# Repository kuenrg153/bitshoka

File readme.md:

```
Open Source is Intrinsic to Bitcoin
```
# The bitshoka V1.0
The Bitshoka V1.0 is based entirely off of the Bitaxe. The only difference are the logos on Schematic and PCB.
Huge shoutout to skot for all the work he did create this project!
The aim Bitshoka V1.0 is to have a Made in Africa Bitcoin miner that works as a platform to get people interested in and familiar with Bitcoin mining.
We hope that this is the first of a number of contributions the Bitshoka team can make to the bitcoin network.

# The bitaxeGamma
bitaxe is a fully open source Bitcoin ASIC miner aimed at decentralizing mining. bitaxeGamma is the 5th major revision of the bitaxe that now includes the BM1370 ASIC from the Antminer S21 Pro

## Goals
- **Easy**: Just plug it in and mine Bitcoin over WiFi. No external computer needed.
- **Practical**: low cost, low noise, low power, low maintenance. You can run this at home.
- **ASIC Power**: High efficiency and hashrate, based on the latest and greatest Application Specific Integrated Circuits.
- **Versatile**: Mine to any StratumV1 pool, Lottery mine, Solo mine, Or hack it to do whatever you want.
- **Bitcoin Ethos**: Fully open source, permissionless and decentralized to support the worldwide freedom money.

## ASIC
At the heart of the bitaxeGamma is a BM1370 Bitcoin mining ASIC from the Antminer S21 Pro from Bitmain. It's not open source.

- Bitmain claims the BM1370 has 15 J/TH efficiency. We can get pretty close to that with the BitaxeGamma
- The Antminer S21 Pro has a nominal hashrate of 234 TH/s. There are 3 hashboards with 65 chips each, for a total of 195 chips. The bitaxeGamma has a single one of these chips. That means _about_ 1.2 TH/s per bitaxeGamma. Initial testing looks good!
- The BM1370 is brand new and isn't available individually yet. The best place to get these chips is right out of a S21 Pro.
- The BM1370 has a different footprint and pinout from the BM1368, BM1366, BM1397 and BM1387 in previous bitaxe.

## Current Status
- BitaxeGamma 600 is working well and has been released!
- In addition to higher hashrate, the Gamma also uses more power. Please pay attemtion to hash frequency and voltage settings as it's much easier to overheat, especially when using the stock heatsink and fan.
- BM1370 firmware support has been added to [esp-miner](https://github.com/skot/esp-miner)
- Be sure to check the [HW issues](https://github.com/skot/bitaxe/issues) for known bugs, reworks and errata.
- This is an _advanced_ build! You can do it, but if you're not looking for a project, it might be best to buy one pre-assembled from one of the [many sellers](https://bitaxe.org/legit.html). Check [Skot's method](assembly.md) of hand assembling PCBs.

## PCB Hardware
This repo contains all of the design files for the PCB. [KiCAD](https://www.kicad.com) software is used. There is a BOM file for all of the components that get soldered to the PCB. 

- Order PCBs from your favorite PCB shop, like [JLCPCB](https://jlcpcb.com), [SeeedStudio](https://www.seeedstudio.com/fusion_pcb.html), or [PCBWay](https://www.pcbway.com)
    - Gerbers are in the `Manufacturing Files` dir. PCBs are 4-layer, 6mil trace/space and 0.3mm hole compatible. 1oz outer / 0.5oz inner layer thickness works well.
    - Make sure to order stencils too. These are the "paste" layers in the gerbers folder. one for top and one for bottom.
- All PCB parts except the ASIC are available from [DigiKey](https://www.digikey.com/en/products) and others. You can find Digikey part numbers on the DK tab of the BOM

## Extra Hardware
There are a few other hardware components that are needed for a complete bitaxe.

- **Heatsink**
	- [40x40mm heatsink and 5V fan](https://www.aliexpress.com/item/2251832861666365.html) from a random AliExpress seller. The fans are crap, but the heatsinks are good.  
- **Fan**
	- You **must** have active cooling on the bitaxe. The heatsink alone is not enough.
	- The Bitaxe has a connector for a 4pin, 5V PWM fan. 40mm square, 20mm thick fans work nicely with the suggested heatsink. Make sure to get a 5V fan! 12V spin, but slowly overheating your Bitaxe..
	- Upgrade your fan with the [Noctua NF-A4x10](https://noctua.at/en/nf-a4x10-5v-pwm) 5V 4-Pin fan for a much more pleasant experience.
- **Thermal compound**
	- Use a good quality thermal compound between the heatsink and ASIC. [Thermal Grizzly Kryonaut](https://www.amazon.com/Thermal-Grizzly-Kryonaut-Grease-Paste/dp/B011F7W3LU) has been known to work well.  
- **Display**
	- Supports 0.91" SSD1306-based I2C OLED Module. [Example Amazon seller](https://www.amazon.com/gp/product/B08ZY4YBHL). Make sure to get the male pins to interface with the Bitaxe PCB. 
- **Power Supply**
	- **5V DC Only!** Anything else will damage the Bitaxe. Be careful and double-check your power supply is 5V. Many other voltage power supplies use the same connector.
	- The power supply needs to supply in excess of 4A (20W) and not drop below 5V. Often times you have to use a power supply rated for 25-30W to get this!
 		- The [Meanwell GST60A05-P1J](https://www.digikey.com/en/products/detail/mean-well-usa-inc/GST60A05-P1J/7703709) at 30 Watts is the cadillac of 5V PSUs and is working well with the Gamma.  
	- The bitaxe uses a 5.5x2.1mm, center-positive barrel jack. 5.5x2.5mm plugs have been known to work.
- **Stand**
	- The PCB has corner mounting holes. You're going to want a stand to mount your Bitaxe. Many excellent 3D printed designs are available.

## Firmware
- The [ESP-Miner](https://github.com/skot/ESP-Miner) has initial support for the BM1370 ASIC. Improvements are ongoing.

### ESP32 Programming Requirements
- As of the bitaxeUltra, all ESP32 programming is done through a USB-C cable and connector on the bitaxe. See [ESP-Miner](https://github.com/skot/ESP-Miner) for more details.

## More Information
- Project page at [bitaxe.org](https://bitaxe.org)
- [Open Source Miners United](discord.gg/osmu) Discord chat
- [building.md](building.md) for PCB ordering tips
- [assembly.md](assembly.md) for assembly tips

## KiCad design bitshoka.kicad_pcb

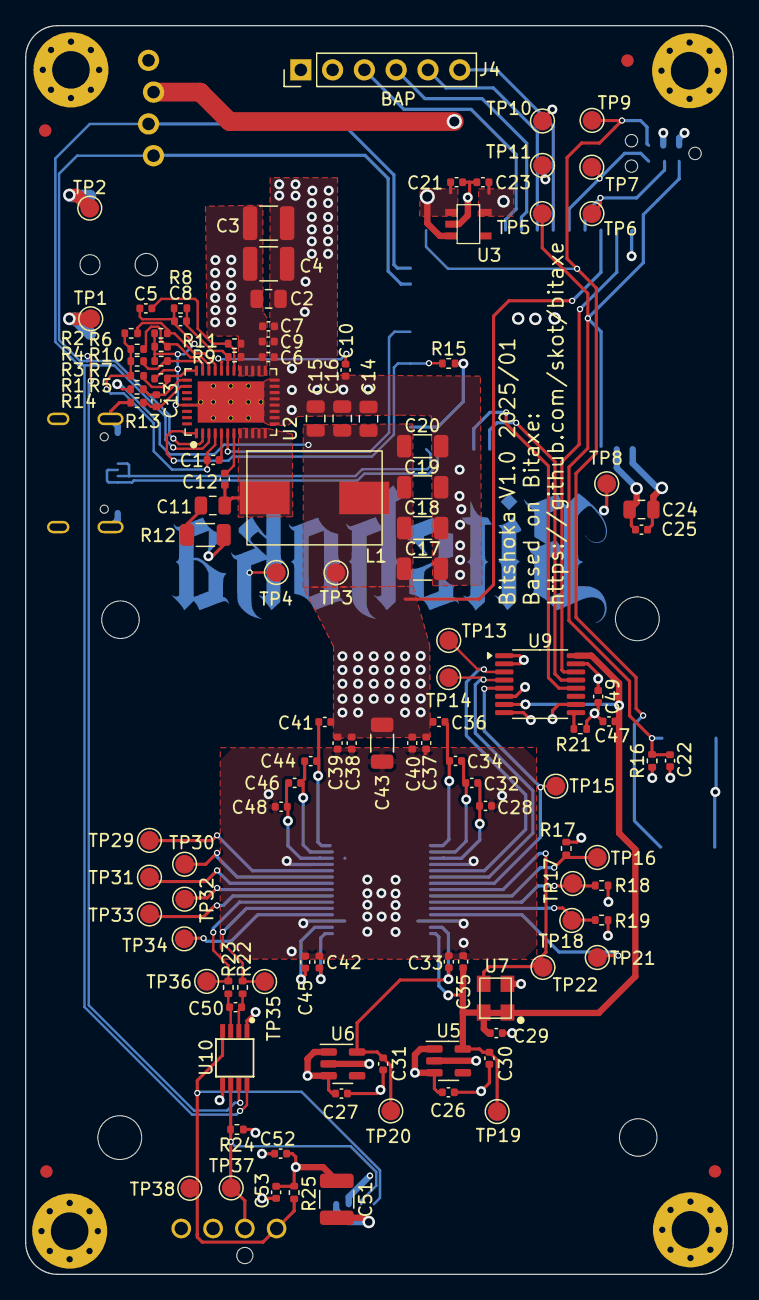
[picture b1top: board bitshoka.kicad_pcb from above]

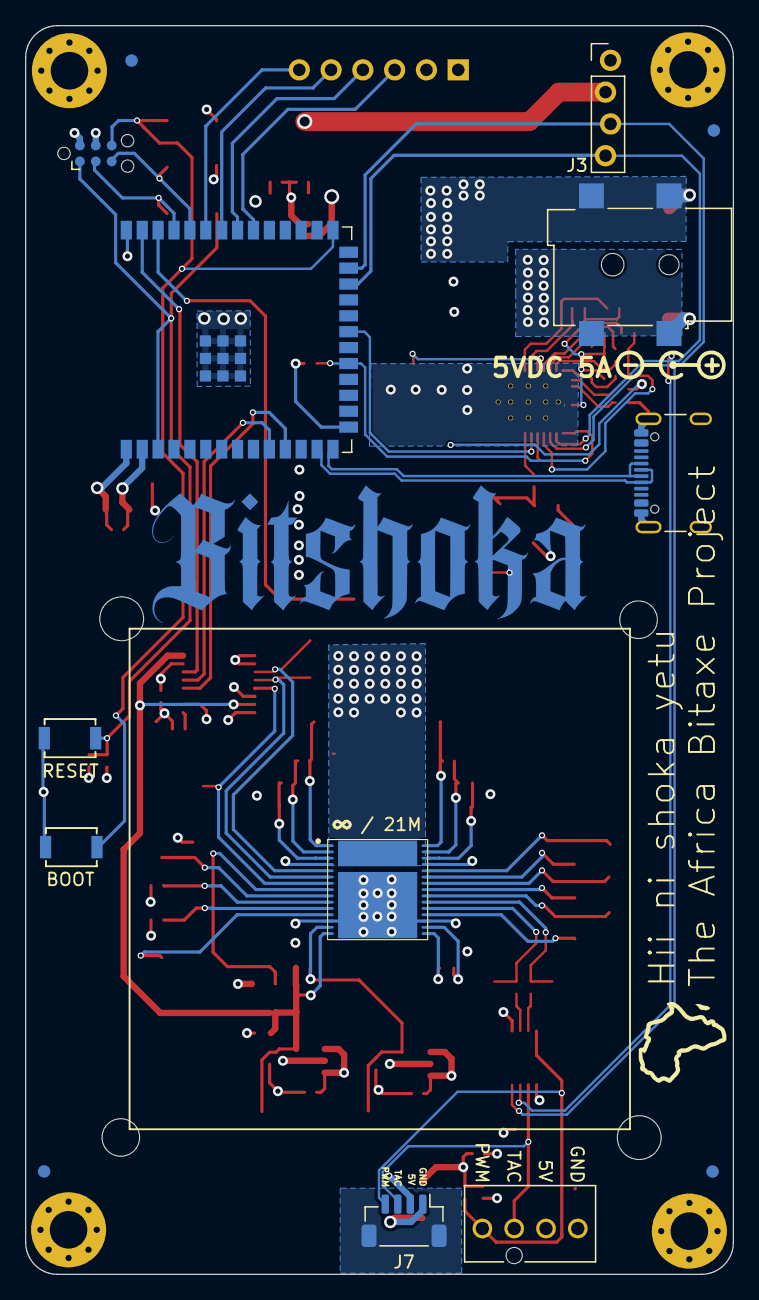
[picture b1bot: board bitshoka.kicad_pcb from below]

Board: 4 copper layers, 56.5 x 99.8 mm, 145 parts (15 on the bottom side), 67 nets.

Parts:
C1, C5, C7, C21, C22, C23, C26, C27, C28, C30, C31, C32, C33, C34, C35, C36, C39, C40, C41, C42, C44, C45, C46, C48: 1uF; C_0402_1005Metric
C2, C24: 10uF; C_0805_2012Metric
C3, C4, C51: 47uF; C_1210_3225Metric
C6: 4700pF; C_0402_1005Metric
C8, C12, C25, C29, C37, C38, C47, C49, C52, C53: 0.1uF; C_0402_1005Metric
C9: 2200pF; C_0402_1005Metric
C10: 4.7uF; C_0402_1005Metric
C11: 1000pF; C_0805_2012Metric
C13: 100pF; C_0402_1005Metric
C14, C15, C16: 22uF; C_0805_2012Metric
C17, C18, C19, C20, C43: 100uF; C_1206_3216Metric
C50: 470pF; C_0402_1005Metric
FID1, FID2, FID3, FID4, FID5, FID6, FID7, FID8: Fiducial; Fiducial_1mm_Mask2mm
H1, H2, H3, H4: MountingHole_Pad; MountingHole_3mm_Pad_Via
H5, H6, H7, H8: MountingHole; MountingHole_3.5mm
J1: 54-00164; TENSILITY_54-00164
J2: TC2030-IDC; Tag-Connect_TC2030-IDC-NL_2x03_P1.27mm_Vertical
J3: Conn_01x04; PinHeader_1x04_P2.54mm_Vertical_shifted
J4: Conn_01x06; PinHeader_1x06_P2.54mm_Vertical
J5: USB_C_Receptacle_USB2.0; USB_C_Receptacle_GCT_USB4105-xx-A
J6: Conn_01x04; 470531000
J7: Conn_01x04; JST_SH_BM04B-SRSS-TB_1x04-1MP_P1.00mm_Vertical
L1: 300nH; SLC1175-271MEC_COC
R1: 8.25k; R_0402_1005Metric
R2, R3, R4, R7: R_0402_1005Metric
R5: 14.7k; R_0402_1005Metric
R6: 0; R_0402_1005Metric
R8: 3.74k; R_0402_1005Metric
R9: 11.8k; R_0402_1005Metric
R10: 68.1k; R_0402_1005Metric
R11: 10; R_0402_1005Metric
R12: 1; R_1206_3216Metric
R13, R14: 49.9; R_0402_1005Metric
R15, R16, R17, R25: 10k; R_0402_1005Metric
R18, R19: 1k; R_0402_1005Metric
R21: 20k; R_0402_1005Metric
R22, R23: 100; R_0402_1005Metric
R24: 5.6k; R_0402_1005Metric
SW1, SW2: GT-TC029B-H025-L1N; SW_CS1213AGF260_CRS
T1: net-tie; NetTie-0.25mm
TP1, TP2, TP3, TP4, TP5, TP6, TP7, TP8, TP9, TP10, TP11, TP13, TP14, TP15, TP16, TP17, TP18, TP19, TP20, TP21, TP22, TP29, TP30, TP31, TP32, TP33, TP34, TP35, TP36, TP37, TP38: TestPoint; TestPoint_Pad_D1.5mm
U1: polarity
U2: TPS546D24ARVFR; LQFN40-CLIP
U3: RT9080-33GJ5
U4: ESP32-S3-WROOM-1
U5: MCP1824T-1202E/OT; SOT-23-5
U6: MCP1824T-0802E; SOT-23-5
U7: 25MHz; SMD3225-4P
U8: BM1370_mode1; BM1370
U9: SN74AVC4T774; TSSOP-16_4.4x5mm_P0.65mm
U10: EMC2101; TSSOP-8_3x3mm_P0.65mm

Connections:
/3V3: C23.1, C24.1, C25.1, C49.1, J2.2, J3.2, R15.2, R16.1, R24.2, TP8.1, TP11.1, U3.5 (VOUT), U4.2 (3V3), U4.15 (GPIO3/TOUCH3/ADC1_CH2*), U9.15 (VCCB), U10.1 (VDD)
/5V: C2.1, C3.1, C4.1, C6.1, C7.1, C9.1, C21.1, C26.1, C27.1, C51.1, C52.1, C53.1, J1.1, J4.1, J6.2, J7.2, R9.1, R11.1, R25.2, TP1.1, U2.21 (PVIN), U2.22 (PVIN), U2.23 (PVIN), U2.24 (PVIN), U2.25 (PVIN), U3.1 (VIN), U3.3 (EN), U5.1 (VIN), U5.3 (EN), U6.1 (VIN), U6.3 (EN)
/BM1370/0V8: C31.1, C33.1, TP20.1, U6.5 (VOUT), U8.14 (VDDIO_08_0)
/BM1370/1V2: C29.2, C30.1, C35.1, C47.1, TP19.1, U5.5 (VOUT), U7.1 (EN), U7.4 (VIN), U8.15 (VDDIO_12_0), U9.7 (DIR3), U9.16 (VCCA)
/BM1370/BI: R17.2, TP16.1, U8.9 (BI)
/BM1370/BO: TP33.1, U8.22 (BO)
/BM1370/CI: TP14.1, U8.6 (CI), U9.4 (A2)
/BM1370/CLKI: TP22.1, U7.3 (OUT), U8.8 (CLKI)
/BM1370/CLKO: TP32.1, U8.23 (CLKO)
/BM1370/CO: TP30.1, U8.25 (CO)
/BM1370/NRSTO: TP29.1, U8.26 (NRSTO)
/BM1370/PIN_MODE: TP34.1, U8.19 (PIN_MODE)
/BM1370/RI: TP31.1, U8.24 (RI)
/BM1370/RO: TP15.1, U8.7 (RO), U9.5 (A3)
/BM1370/RST_N: TP13.1, U8.5 (NRSTI), U9.3 (A1)
/BM1370/VDD1_0: C34.2, C36.1, U8.1 (VDD3_0)
/BM1370/VDD1_1: C41.2, C44.1, U8.30 (VDD3_1)
/BM1370/VDD2_0: C32.2, C34.1, U8.2 (VDD2_0)
/BM1370/VDD2_1: C44.2, C46.1, U8.29 (VDD2_1)
/BM1370/VDD3_0: C28.2, C32.1, U8.3 (VDD1_0)
/BM1370/VDD3_1: C46.2, C48.1, U8.28 (VDD1_1)
/ESP32/EN: C22.1, J2.1, R16.2, SW1.2, TP5.1, U4.3 (EN)
/ESP32/IO0: J2.6, SW2.2, TP9.1, U4.27 (GPIO0/BOOT*)
/ESP32/P_RX: J2.5, TP7.1, U4.36 (U0RXD/GPIO44/CLK_OUT2)
/ESP32/P_TX: J2.3, TP6.1, U4.37 (U0TXD/GPIO43/CLK_OUT1)
/ESP32/USB_D+: J5.A6 (D+), J5.B6 (D+), U4.14 (GPIO20/U1CTS/ADC2_CH9/CLK_OUT1/USB_D+)
/ESP32/USB_D-: J5.A7 (D-), J5.B7 (D-), U4.13 (GPIO19/U1RTS/ADC2_CH8/CLK_OUT2/USB_D-)
/Fan/FAN_PWM: J6.4, J7.4, R25.1, TP38.1, U10.4 (FAN)
/Fan/FAN_TACH: J6.3, J7.3, R24.1, TP37.1, U10.6 (ALERT/TACH)
/Fan/TEMP_DN: C50.2, R22.1, U10.3 (DN)
/Fan/TEMP_DP: C50.1, R23.2, U10.2 (DP)
/Fan/TEMP_N: R22.2, TP36.1, U8.21 (TEMP_N)
/Fan/TEMP_P: R23.1, TP35.1, U8.20 (TEMP_P)
/Power/AGND: C5.1, C8.2, R5.1, R6.2, R7.2, R8.2, R10.2, T1.1, U2.37 (AGND)
/Power/PGOOD: R15.1, U2.1 (PGD), U4.19 (GPIO11/TOUCH11/ADC2_CH0/FSPID/FSPIIO5/S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)
/Power/PMB_ALRT: U2.6 (SMB_ALRT), U4.21 (GPIO13/TOUCH13/ADC2_CH2/FSPIQ/FSPIIO7/S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)
/Power/SW: C11.2, C12.2, L1.1, U2.8 (SW), U2.9 (SW), U2.10 (SW), U2.11 (SW), U2.12 (SW)
/RST: U4.39 (GPIO1/TOUCH1/ADC1_CH0), U9.14 (B1)
/RX: U4.11 (GPIO18/U1RXD/ADC2_CH7/CLK_OUT3), U9.12 (B3)
/SCL: J3.3, U2.3 (PMB_CLK), U4.25 (GPIO48/SPICLK_N/SUBSPICLK_N_DIFF), U10.8 (SMCLK)
/SDA: J3.4, U2.2 (PMB_DATA), U4.24 (GPIO47/SPICLK_P/SUBSPICLK_P_DIFF), U10.7 (SMDATA)
/TX: U4.10 (GPIO17/U1TXD/ADC2_CH6), U9.13 (B2)
/VDD: C14.1, C15.1, C16.1, C17.1, C18.1, C19.1, C20.1, C36.2, C37.1, C38.1, C39.1, C40.1, C41.1, C43.1, L1.2, R14.1, TP3.1, U4.38 (GPIO2/TOUCH2/ADC1_CH1), U8.31 (VDD)
GND: C2.2, C3.2, C4.2, C6.2, C7.2, C9.2, C10.2, C14.2, C15.2, C16.2, C17.2, C18.2, C19.2, C20.2, C21.2, C22.2, C23.2, C24.2, C25.2, C26.2, C27.2, C28.1, C29.1, C30.2, C31.2, C33.2, C35.2, C37.2, C38.2, C39.2, C40.2, C42.2, C43.2, C45.2, C47.2, C48.2, C49.2, C51.2, C52.2, C53.2, H1.1, H2.1, H3.1, H4.1, J1.2, J1.3, J2.4, J3.1, J4.2, J5.A1 (GND), J5.B1 (GND), J5.S1 (SHIELD), J6.1, J7.1, R12.1, R13.2, R17.1, R18.1, R19.1, R21.1, SW1.1, SW2.1, T1.2, TP2.1, TP4.1, TP10.1, U2.13 (PGND), U2.14 (PGND), U2.15 (PGND), U2.16 (PGND), U2.17 (PGND), U2.18 (PGND), U2.19 (PGND), U2.20 (PGND), U2.41 (PAD), U3.2 (GND), U4.1 (GND), U4.40 (GND), U4.41 (GND), U5.2 (GND), U6.2 (GND), U7.2 (GND), U8.4 (VSS), U8.13 (PLL_VSS), U8.18 (VSS), U8.27 (VSS), U8.32 (VSS), U9.1 (DIR1), U9.2 (DIR2), U9.6 (A4), U9.8 (DIR4), U9.10 (GND), U10.5 (GND)
unnamed: C11.1, R12.2
unnamed: J4.3, U4.32 (MTCK/GPIO39/CLK_OUT3/SUBSPICS1)
unnamed: J4.4, U4.33 (MTDO/GPIO40/CLK_OUT2)
unnamed: J4.5, U4.34 (MTDI/GPIO41/CLK_OUT1)
unnamed: J4.6, U4.35 (MTMS/GPIO42)
unnamed: R3.2, R7.1, U2.31 (ADRSEL)
unnamed: C5.2, R11.2, U2.26 (AVIN)
unnamed: C12.1, U2.7 (BOOT)
unnamed: C1.2, R1.1, R2.1, R3.1, R4.1, U2.4 (BP1V5)
unnamed: C1.1, U2.5 (DRTN)
unnamed: C8.1, R8.1, R9.2, U2.27 (EN/UVLO)
unnamed: C13.2, R13.1, U2.34 (GOSNS)
unnamed: R1.2, R5.2, U2.32 (MSEL1)
unnamed: R2.2, R6.1, U2.29 (MSEL2)
unnamed: C10.1, U2.28 (VDD5)
unnamed: C13.1, R14.2, U2.33 (VOSNS)
unnamed: R4.2, R10.1, U2.30 (VSEL)
unnamed: TP21.1, U8.12 (INV_CLKO)
unnamed: R19.2, TP18.1, U8.11 (LITE_PAD)
unnamed: R18.2, TP17.1, U8.10 (ROSC_SEL)
unnamed: C45.1, U8.17 (VDDIO_08_1)
unnamed: C42.1, U8.16 (VDDIO_12_1)
unnamed: R21.2, U9.9 (OE)

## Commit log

2025-01-20 Conversion of Bitaxe to Bitshoka
    This project is a COMPLETE copy of the Bitaxe Gamma project https://github.com/bitaxeorg/bitaxeGamma
    I only changed some of the artwork on the bottom copper, mask and top and bottom silk layers.
    Use at your own peril!
2025-01-20 Getting rid of Bitaxe kicad files
2025-01-20 Updating the Readme
